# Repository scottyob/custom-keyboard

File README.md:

# custom-keyboard
My very first custom keyboard!

## Goals
* Be really quick to change machines from a work computer, personal computer, and embedded computer
* Have an embeded display for e-mails and custom notifications.

## Designing
[Keyboard Layout Editor](http://www.keyboard-layout-editor.com/) is used to build the layout
[PCB Generator](https://builder.mrkeebs.com/) is used to build the base KiCad templates - Not working
[KiCad plugin](https://github.com/adamws/kicad-kbplacer) Maybe this

## Inspiration
https://github.com/overlordpro-sys/keycool84keyboard
[Designers Guide](https://wiki.ai03.com/books/pcb-design/chapter/pcb-designer-guide)
[Great YouTube Design](https://www.youtube.com/watch?v=8WXpGTIbxlQ) (plus, his name is Scotto!)

## Display options
* This looks small enough and has a large enough resolution to be useful:  https://www.amazon.com/Portable-Computer-Temperature-Raspberry-Monitoring/dp/B0C5CJSM3B/ref=sr_1_15?crid=1Z2TTTSMCJ9M3&dib=eyJ2IjoiMSJ9.twG_gHx_7npwcecLIDkTMz68C16EEFkX2myDhWZpakM4PwJHDKMsepyzzZx5_fr-Fv0QWtuMAJvjoFRniusn_2mAP8U1p1KvTDTy_nIf5XBhxKDMTtR6kEIH5bDDDC3kfiqdF0MrOl_FwFwhKsGs7nZMyqzwkf1SLikeBaauqQMlMwHEYTlBRP9wpbAJ9CpN7bQet1QICcqR2IB1Qb4BmEeEdJr8Al8KNutdiwxeoi11xH34oSaYqEw22Ke8fPJI00CEKSvfC8BukvGODd5jw-uKOd0040SWEzb48uFr6ig.ORM6r5WaZxyWdhVOk3N-LtFBRF50ZFboxtpqMb3Jbdg&dib_tag=se&keywords=stretched%2Bbar%2Bdisplay&qid=1719265894&sprefix=stretched%2Bbar%2Bdisplay%2Caps%2C145&sr=8-15&th=1

## Log
The KeyCool 84 model was used

## BOM
Keys:  https://www.amazon.com/Ranked-Ks-33-Switches-Mechanical-Keyboards/dp/B09WYFZ9RW?source=ps-sl-shoppingads-lpcontext&ref_=fplfs&smid=AH4D7YJ4IREB6&th=1

Switches:  Keychron Low-Profile Keychron Optical White Switch Set:  https://www.amazon.com/Keychron-Low-Profile-Optical-White-Switch/dp/B09F8N5671/ref=asc_df_B09F8N5671/?tag=hyprod-20&linkCode=df0&hvadid=692875362841&hvpos=&hvnetw=g&hvrand=16111957698866127215&hvpone=&hvptwo=&hvqmt=&hvdev=c&hvdvcmdl=&hvlocint=&hvlocphy=9031967&hvtargid=pla-2281435178578&mcid=0d9c4b6c974f36919238ca352fcf1e5d&hvocijid=16111957698866127215-B09F8N5671-&hvexpln=73&gad_source=1&th=1

---
Keys:  https://nuphy.com/products/nuphy-wisteria-t55-low-profile-switches?variant=40519244185709&currency=USD&utm_medium=product_sync&utm_source=google&utm_content=sag_organic&utm_campaign=sag_organic&cmp_id=20374253646&adg_id=&kwd=&device=c&gad_source=1&gclid=CjwKCAjw-O6zBhASEiwAOHeGxY04Fqa9ekofnuaXTJEuknBaLYsXi4nRFtKgb14qA1gg2Q-BrQMgmBoCAmcQAvD_BwE

[200~NuPhy Wisteria Low-profile Switches

**You'll want Gateron KS-33**

Use These:  https://shop.beekeeb.com/product/gateron-low-profile-hotswap-socket/
With this footprint:  https://github.com/siderakb/key-switches.pretty?tab=readme-ov-file#user-content-fn-pth-25bb5443dc34dca477740638b10eb813

Guides:
https://github.com/ebastler/zmk-designguide
this recommends holyiot 18010 or moko mk08a. other people fiddle around with stuff like xiao nrf or even nice!nano (or nice!nano clones)

Keycaps perhaps:
- These are not shine through, but I like them!  https://www.amazon.com/Chocfox-Keyboard-Switches-Mechanical-white-134Keys/dp/B0CQ1ZHDP8/ref=sims_dp_d_dex_ai_speed_loc_mtl-v2_v1_d_sccl_2_5/139-4689362-5463854?pd_rd_w=tRYy4&content-id=amzn1.sym.970de5f6-e09a-4fcf-80c0-0a0041912886&pf_rd_p=970de5f6-e09a-4fcf-80c0-0a0041912886&pf_rd_r=KBXG3AW2HWJMRZ1WNTVA&pd_rd_wg=QhR4F&pd_rd_r=f35a1bc3-d88b-4c73-8d4c-3228ac4289e8&pd_rd_i=B0CQ1ZHDP8&psc=1

- Yeah, I think these keycaps:  https://www.amazon.com/XVX-Profile-Keyboard-Switches-Mechanical/dp/B0BVYV67QS/ref=pd_bxgy_thbs_d_sccl_1/139-4689362-5463854?pd_rd_w=X4Tbp&content-id=amzn1.sym.60707ad7-5cf4-45ed-b044-7f953897a39a&pf_rd_p=60707ad7-5cf4-45ed-b044-7f953897a39a&pf_rd_r=VAWAKCYHR6X9TYQKH0A8&pd_rd_wg=gBP03&pd_rd_r=466d4956-36b8-48f1-ac49-e200315451c7&pd_rd_i=B0BVYV67QS&psc=1

 - Controller

Probably this:  https://makerdiary.com/products/nrf52840-connectkit?variant=43255093035163

# Setup
1. Install [This Plugin](https://github.com/ebastler/marbastlib)
2. 

Footprint for KS-33:  https://shop.beekeeb.com/product/gateron-low-profile-hotswap-socket/

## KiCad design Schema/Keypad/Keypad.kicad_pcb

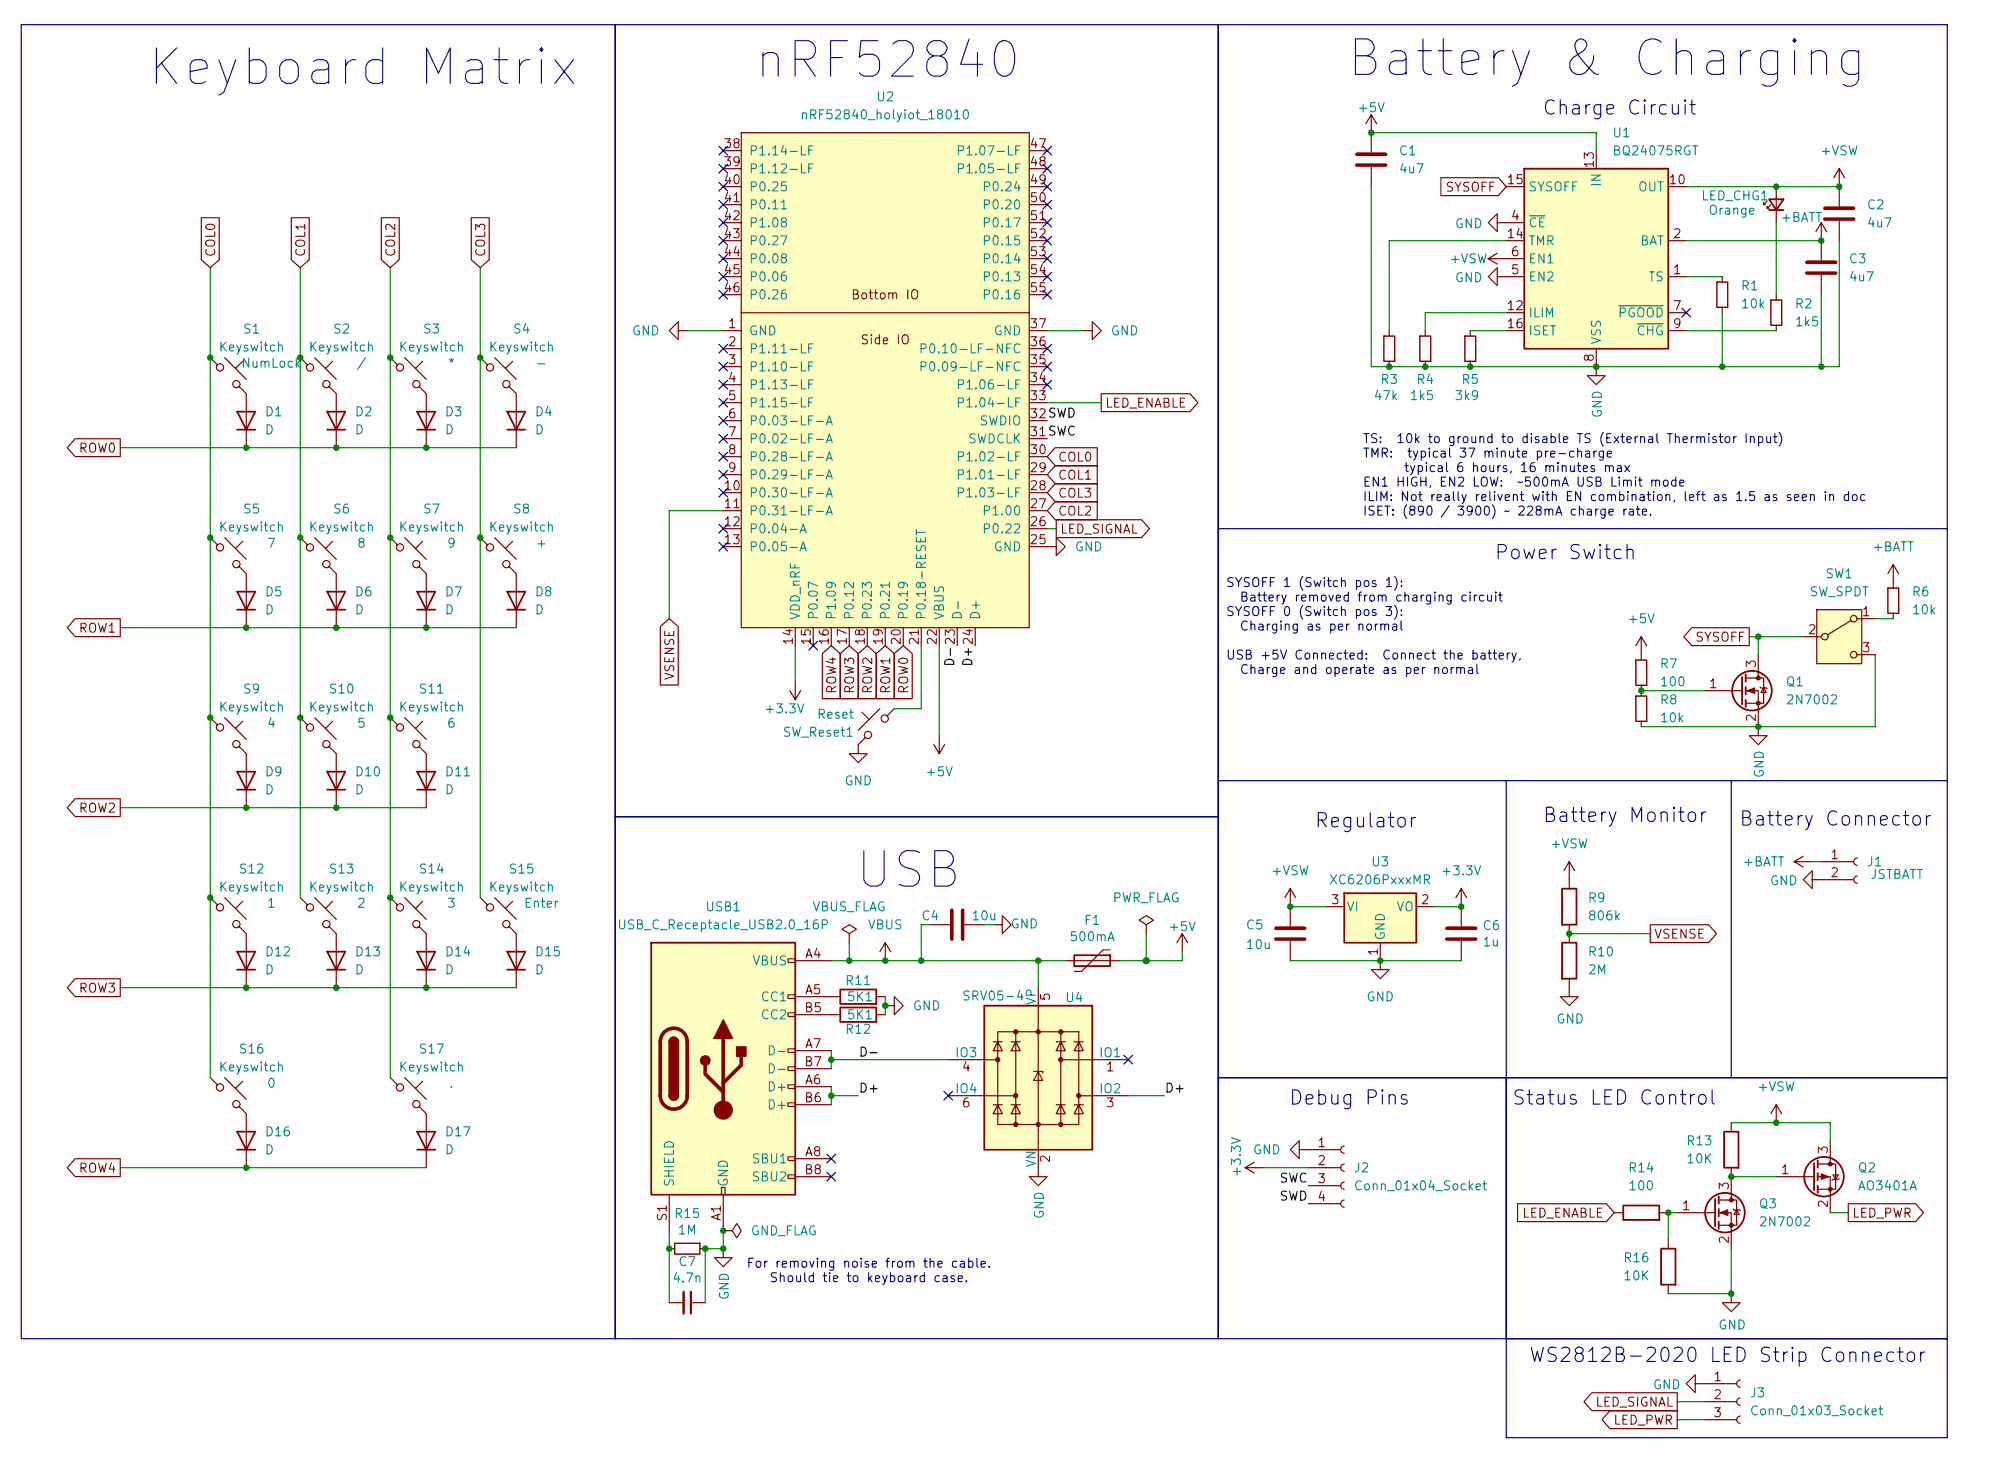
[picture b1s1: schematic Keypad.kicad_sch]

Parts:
C1, C2, C3: 4u7; C_0603_1608Metric
C4, C5: 10u; C_0603_1608Metric; MPN CL10A106KP8NNNC; JLCSMT C19702
C6: 1u; C_0603_1608Metric; MPN CL10A105KB8NNNC; LCSC C15849
C7: 4.7n; C_0805_2012Metric
D1, D2, D3, D4, D5, D6, D7, D8, D9, D10, D11, D12, D13, D14, D15, D16, D17: D; Diode_SOD-123
F1: 500mA; Fuse_0805_2012Metric; MPN SMD0805-050; JLCSMT C66452
J1: JSTBATT; JST_PH_S2B-PH-K_1x02_P2.00mm_Horizontal
J2: Conn_01x04_Socket; PinHeader_1x04_P2.54mm_Vertical
J3: Conn_01x03_Socket; PinSocket_1x03_P2.54mm_Vertical
LED_CHG1: Orange; LED_0603_1608Metric_Pad1.05x0.95mm_HandSolder
Q1, Q3: 2N7002; SOT-23
Q2: AO3401A; SOT-23
R1, R6, R8: 10k; R_0603_1608Metric_Pad0.98x0.95mm_HandSolder
R2, R4: 1k5; R_0603_1608Metric_Pad0.98x0.95mm_HandSolder
R3: 47k; R_0603_1608Metric_Pad0.98x0.95mm_HandSolder
R5: 3k9; R_0603_1608Metric_Pad0.98x0.95mm_HandSolder
R7, R14: 100; R_0603_1608Metric_Pad0.98x0.95mm_HandSolder
R9: 806k; R_0603_1608Metric_Pad0.98x0.95mm_HandSolder
R10: 2M; R_0603_1608Metric_Pad0.98x0.95mm_HandSolder
R11, R12: 5K1; R_0603_1608Metric_Pad0.98x0.95mm_HandSolder
R13, R16: 10K; R_0603_1608Metric_Pad0.98x0.95mm_HandSolder
R15: 1M; R_0603_1608Metric_Pad0.98x0.95mm_HandSolder
S1, S2, S3, S4, S5, S6, S7, S8, S9, S10, S11, S12, S13, S14, S15, S16, S17: Keyswitch; SW_KS33_HS_KS-2P02B01-02_HS_1u
SW1: SW_SPDT; SW_MSK12C02-HB
SW_Reset1: Reset; SW_Push_1P1T_NO_6x6mm_H9.5mm
U1: BQ24075RGT; VQFN-16-1EP_3x3mm_P0.5mm_EP1.6x1.6mm
U2: nRF52840_holyiot_18010
U3: XC6206PxxxMR; SOT-23-3
U4: SRV05-4; SOT-23-6; MPN SRV05-4-P-T7; JLCSMT C85364
USB1: USB_C_Receptacle_USB2.0_16P; USB_C_Receptacle_HRO_TYPE-C-31-M-12

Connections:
+3.3V: C6.2, J2.2, U2.14 (VDD_nRF), U3.2 (VO)
+5V: C1.1, F1.1, R7.1, U1.13 (IN), U2.22 (VBUS)
+BATT: C3.1, J1.1, R6.1, U1.2 (BAT), U1.3 (BAT)
+VSW: C2.1, C5.1, LED_CHG1.2 (A), Q2.3 (D), R9.1, R13.1, U1.6 (EN1), U1.10 (OUT), U1.11 (OUT), U3.3 (VI)
/D+: U2.24 (D+), U4.3 (IO2), USB1.A6 (D+), USB1.B6 (D+)
/D-: U2.23 (D-), U4.4 (IO3), USB1.A7 (D-), USB1.B7 (D-)
/SWC: J2.3, U2.31 (SWDCLK)
/SWD: J2.4, U2.32 (SWDIO)
COL0: S1.1, S5.1, S9.1, S12.1, S16.1, U2.30 (P1.02-LF)
COL1: S2.1, S6.1, S10.1, S13.1, U2.29 (P1.01-LF)
COL2: S3.1, S7.1, S11.1, S14.1, S17.1, U2.27 (P1.00)
COL3: S4.1, S8.1, S15.1, U2.28 (P1.03-LF)
GND: C1.2, C2.2, C3.2, C4.1, C5.2, C6.1, C7.1, J1.2, J2.1, J3.1, Q1.2 (S), Q3.2 (S), R1.2, R3.2, R4.2, R5.2, R8.2, R10.2, R11.2, R12.2, R15.1, R16.2, SW1.3 (C), SW_Reset1.1, U1.4 (~CE), U1.5 (EN2), U1.8 (VSS), U1.17 (VSS), U2.1 (GND), U2.25 (GND), U2.37 (GND), U3.1 (GND), U4.2 (VN), USB1.A1 (GND), USB1.A12 (GND), USB1.B1 (GND), USB1.B12 (GND)
LED_ENABLE: R14.1, U2.33 (P1.04-LF)
LED_PWR: J3.3, Q2.2 (S)
LED_SIGNAL: J3.2, U2.26 (P0.22)
unnamed: D1.2 (A), S1.2
unnamed: D2.2 (A), S2.2
unnamed: D3.2 (A), S3.2
unnamed: D4.2 (A), S4.2
unnamed: D5.2 (A), S5.2
unnamed: D6.2 (A), S6.2
unnamed: D7.2 (A), S7.2
unnamed: D8.2 (A), S8.2
unnamed: D9.2 (A), S9.2
unnamed: D10.2 (A), S10.2
unnamed: D11.2 (A), S11.2
unnamed: D12.2 (A), S12.2
unnamed: D13.2 (A), S13.2
unnamed: D14.2 (A), S14.2
unnamed: D15.2 (A), S15.2
unnamed: D16.2 (A), S16.2
unnamed: D17.2 (A), S17.2
unnamed: LED_CHG1.1 (K), R2.1
unnamed: Q1.1 (G), R7.2, R8.1
unnamed: Q2.1 (G), Q3.3 (D), R13.2
unnamed: Q3.1 (G), R14.2, R16.1
unnamed: R6.2, SW1.1 (A)
unnamed: R4.1, U1.12 (ILIM)
unnamed: R5.1, U1.16 (ISET)
unnamed: R3.1, U1.14 (TMR)
unnamed: R1.1, U1.1 (TS)
unnamed: R2.2, U1.9 (~CHG)
unnamed: SW_Reset1.2, U2.21 (P0.18-RESET)
unnamed: R11.1, USB1.A5 (CC1)
unnamed: R12.1, USB1.B5 (CC2)
unnamed: C7.2, R15.2, USB1.S1 (SHIELD)
ROW0: D1.1 (K), D2.1 (K), D3.1 (K), D4.1 (K), U2.20 (P0.19)
ROW1: D5.1 (K), D6.1 (K), D7.1 (K), D8.1 (K), U2.19 (P0.21)
ROW2: D9.1 (K), D10.1 (K), D11.1 (K), U2.18 (P0.23)
ROW3: D12.1 (K), D13.1 (K), D14.1 (K), D15.1 (K), U2.17 (P0.12)
ROW4: D16.1 (K), D17.1 (K), U2.16 (P1.09)
SYSOFF: Q1.3 (D), SW1.2 (B), U1.15 (SYSOFF)
VBUS: C4.2, F1.2, U4.5 (VP), USB1.A4 (VBUS), USB1.A9 (VBUS), USB1.B4 (VBUS), USB1.B9 (VBUS)
VSENSE: R9.2, R10.1, U2.11 (P0.31-LF-A)

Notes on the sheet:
Status LED Control
WS2812B-2020 LED Strip Connector
USB
Battery & Charging
nRF52840
Charge Circuit
Battery Connector
Power Switch
Keyboard Matrix
SYSOFF 1 (Switch pos 1): Battery removed from charging circuit SYSOFF 0 (Switch pos 3): Charging as per normal USB +5V Connected: Connect the battery, Charge and operate as per normal
Debug Pins
For removing noise from the cable. Should tie to keyboard case.
Battery Monitor
Regulator
TS: 10k to ground to disable TS (External Thermistor Input) TMR: typical 37 minute pre-charge typical 6 hours, 16 minutes max EN1 HIGH, EN2 LOW: ~500mA USB Limit mode ILIM: Not really relivent with EN combination, left as 1.5 as seen in doc ISET: (890 / 3900) ~ 228mA charge rate.

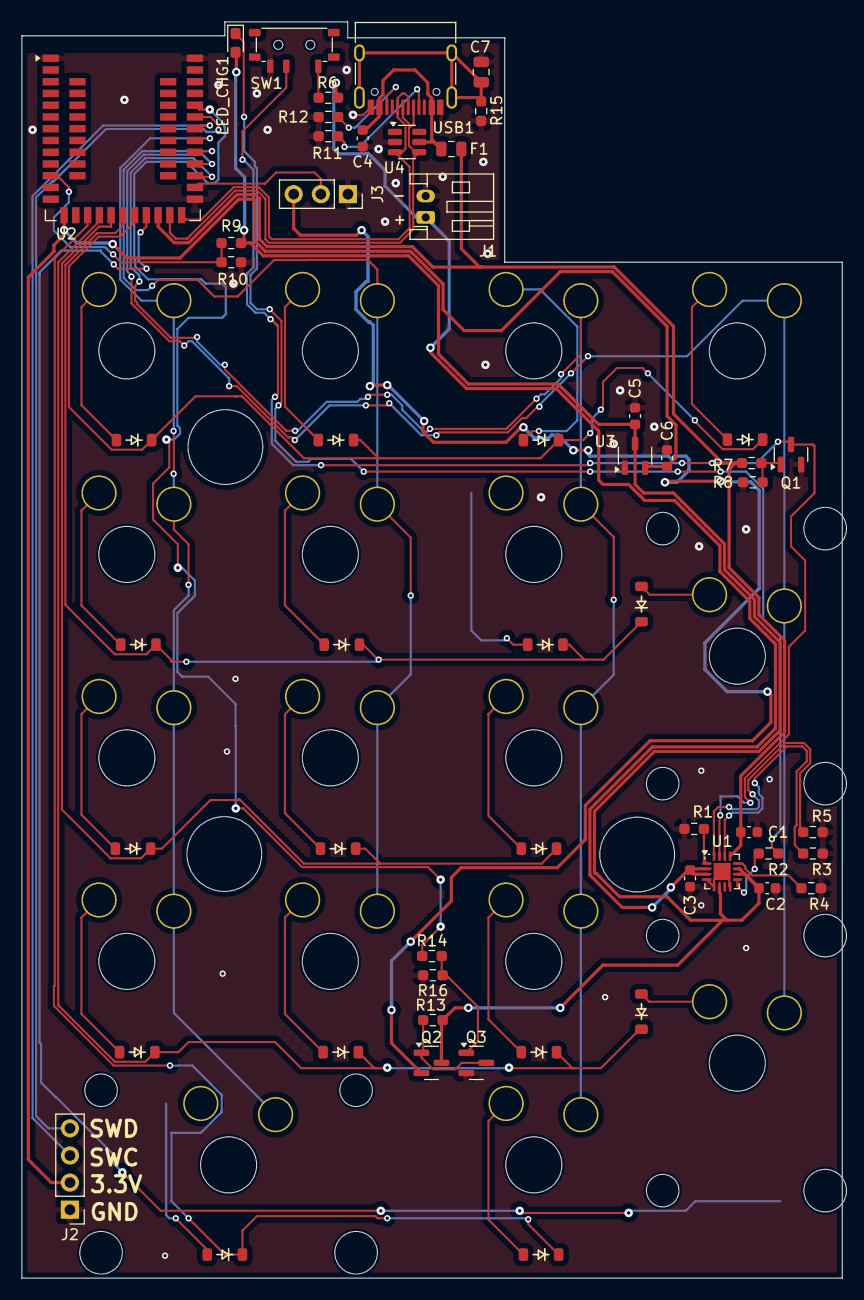
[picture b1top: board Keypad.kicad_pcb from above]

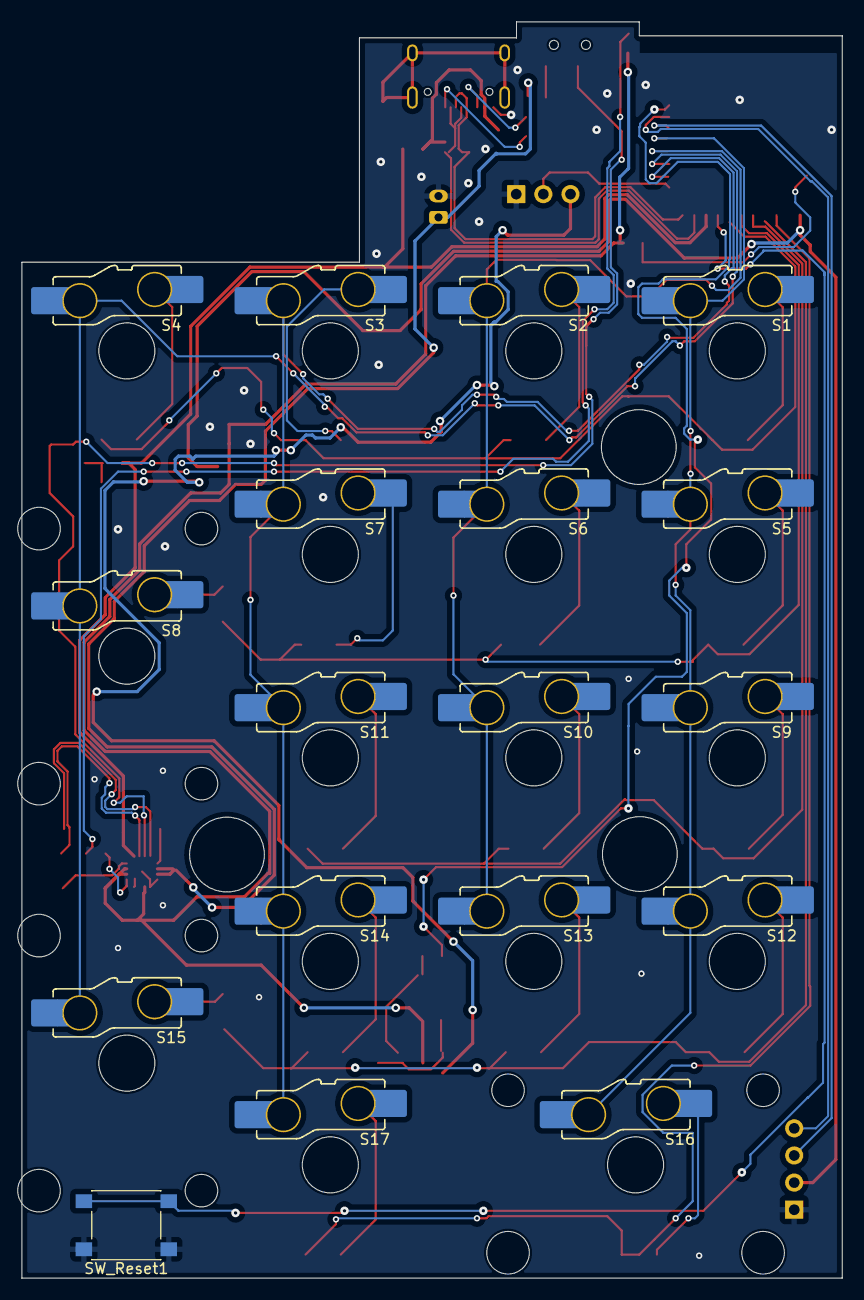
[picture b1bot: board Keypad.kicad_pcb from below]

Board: 2 copper layers, 76.8 x 117.6 mm, 72 parts (18 on the bottom side), 55 nets.

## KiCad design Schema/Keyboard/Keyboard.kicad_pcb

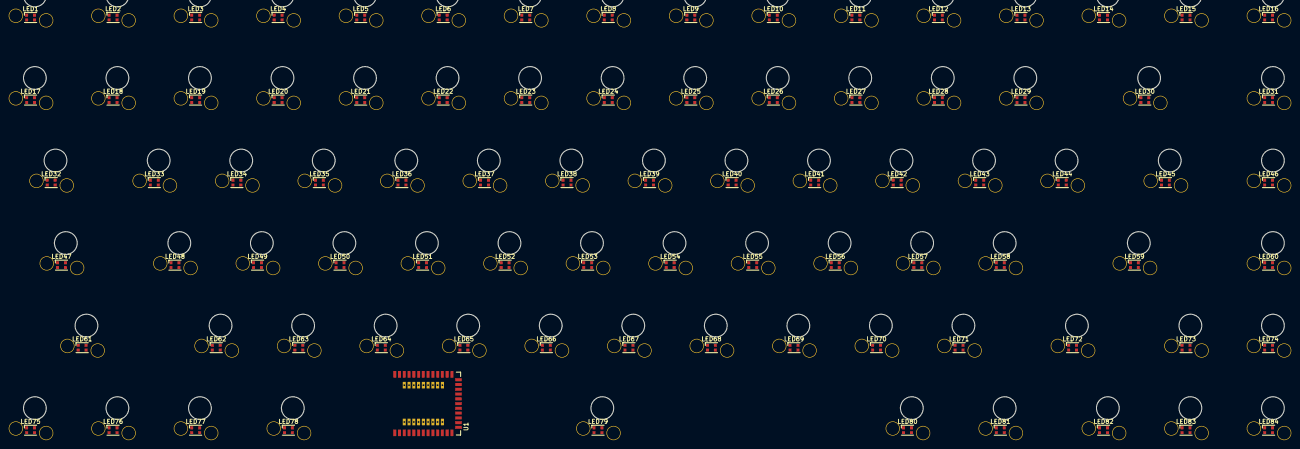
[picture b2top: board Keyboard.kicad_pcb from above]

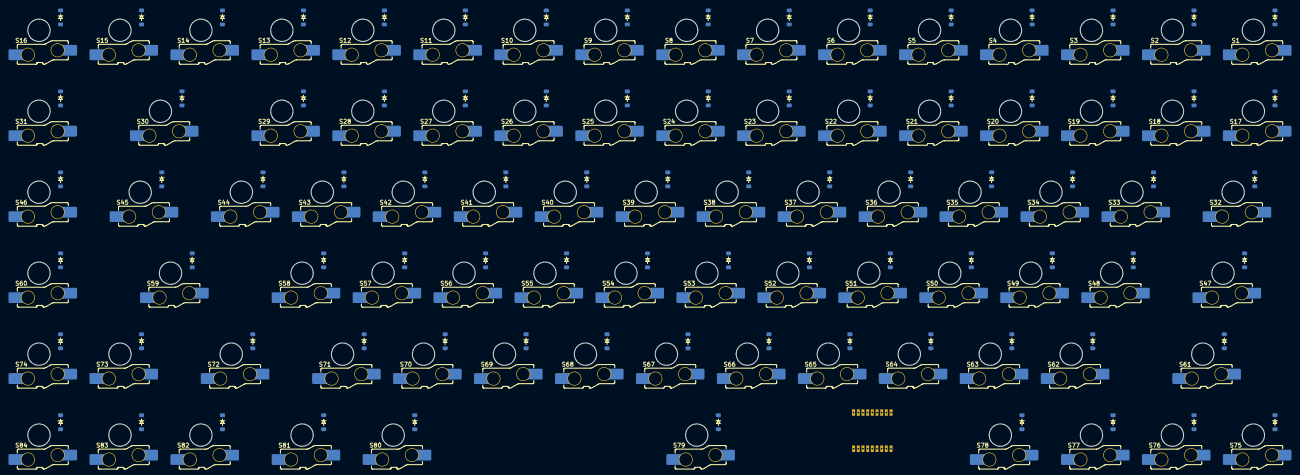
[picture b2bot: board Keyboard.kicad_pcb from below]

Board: 2 copper layers, 253 parts (168 on the bottom side), 191 nets, no tracks yet.

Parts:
D1, D2, D3, D4, D5, D6, D7, D8, D9, D10, D11, D12, D13, D14, D15, D16, D17, D18, D19, D20, D21, D22, D23, D24, D25, D26, D27, D28, D29, D30, D31, D32, D33, D34, D35, D36, D37, D38, D39, D40, D41, D42, D43, D44, D45, D46, D47, D48, D49, D50, D51, D52, D53, D54, D55, D56, D57, D58, D59, D60, D61, D62, D63, D64, D65, D66, D67, D68, D69, D70, D71, D72, D73, D74, D75, D76, D77, D78, D79, D80, D81, D82, D83, D84: D; Diode_SOD-123
LED1, LED2, LED3, LED4, LED5, LED6, LED7, LED8, LED9, LED10, LED11, LED12, LED13, LED14, LED15, LED16, LED17, LED18, LED19, LED20, LED21, LED22, LED23, LED24, LED25, LED26, LED27, LED28, LED29, LED30, LED31, LED32, LED33, LED34, LED35, LED36, LED37, LED38, LED39, LED40, LED41, LED42, LED43, LED44, LED45, LED46, LED47, LED48, LED49, LED50, LED51, LED52, LED53, LED54, LED55, LED56, LED57, LED58, LED59, LED60, LED61, LED62, LED63, LED64, LED65, LED66, LED67, LED68, LED69, LED70, LED71, LED72, LED73, LED74, LED75, LED76, LED77, LED78, LED79, LED80, LED81, LED82, LED83, LED84: WS2812B-2020; LED_WS2812B-2020_PLCC4_2.0x2.0mm
S1, S2, S3, S4, S5, S6, S7, S8, S9, S10, S11, S12, S13, S14, S15, S16, S17, S18, S19, S20, S21, S22, S23, S24, S25, S26, S27, S28, S29, S30, S31, S32, S33, S34, S35, S36, S37, S38, S39, S40, S41, S42, S43, S44, S45, S46, S47, S48, S49, S50, S51, S52, S53, S54, S55, S56, S57, S58, S59, S60, S61, S62, S63, S64, S65, S66, S67, S68, S69, S70, S71, S72, S73, S74, S75, S76, S77, S78, S79, S80, S81, S82, S83, S84: Keyswitch; SW_KS33_HS_KS-2P02B01-02_HS_1u
U1: nRF52840_holyiot_18010

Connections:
+5V: LED1.4 (VDD), LED2.4 (VDD), LED3.4 (VDD), LED4.4 (VDD), LED5.4 (VDD), LED6.4 (VDD), LED7.4 (VDD), LED8.4 (VDD), LED9.4 (VDD), LED10.4 (VDD), LED11.4 (VDD), LED12.4 (VDD), LED13.4 (VDD), LED14.4 (VDD), LED15.4 (VDD), LED16.4 (VDD), LED17.4 (VDD), LED18.4 (VDD), LED19.4 (VDD), LED20.4 (VDD), LED21.4 (VDD), LED22.4 (VDD), LED23.4 (VDD), LED24.4 (VDD), LED25.4 (VDD), LED26.4 (VDD), LED27.4 (VDD), LED28.4 (VDD), LED29.4 (VDD), LED30.4 (VDD), LED31.4 (VDD), LED32.4 (VDD), LED33.4 (VDD), LED34.4 (VDD), LED35.4 (VDD), LED36.4 (VDD), LED37.4 (VDD), LED38.4 (VDD), LED39.4 (VDD), LED40.4 (VDD), LED41.4 (VDD), LED42.4 (VDD), LED43.4 (VDD), LED44.4 (VDD), LED45.4 (VDD), LED46.4 (VDD), LED47.4 (VDD), LED48.4 (VDD), LED49.4 (VDD), LED50.4 (VDD), LED51.4 (VDD), LED52.4 (VDD), LED53.4 (VDD), LED54.4 (VDD), LED55.4 (VDD), LED56.4 (VDD), LED57.4 (VDD), LED58.4 (VDD), LED59.4 (VDD), LED60.4 (VDD), LED61.4 (VDD), LED62.4 (VDD), LED63.4 (VDD), LED64.4 (VDD), LED65.4 (VDD), LED66.4 (VDD), LED67.4 (VDD), LED68.4 (VDD), LED69.4 (VDD), LED70.4 (VDD), LED71.4 (VDD), LED72.4 (VDD), LED73.4 (VDD), LED74.4 (VDD), LED75.4 (VDD), LED76.4 (VDD), LED77.4 (VDD), LED78.4 (VDD), LED79.4 (VDD), LED80.4 (VDD), LED81.4 (VDD), LED82.4 (VDD), LED83.4 (VDD), LED84.4 (VDD)
COL0: S1.1, S17.1, S32.1, S47.1, S75.1
COL1: S2.1, S18.1, S61.1, S76.1
COL2: S3.1, S19.1, S33.1, S48.1, S62.1, S77.1
COL3: S4.1, S20.1, S34.1, S49.1, S63.1, S78.1
COL4: S5.1, S21.1, S35.1, S50.1, S64.1
COL5: S6.1, S22.1, S36.1, S51.1, S65.1
COL6: S7.1, S23.1, S37.1, S52.1, S66.1, S79.1
COL7: S8.1, S24.1, S38.1, S53.1, S67.1
COL8: S9.1, S25.1, S39.1, S54.1, S68.1
COL9: S10.1, S26.1, S40.1, S55.1, S69.1
COL10: S11.1, S27.1, S41.1, S56.1, S70.1, S80.1
COL11: S12.1, S28.1, S42.1, S57.1, S71.1, S81.1
COL12: S13.1, S29.1, S43.1, S58.1
COL13: S14.1, S44.1, S59.1, S72.1, S82.1
COL14: S15.1, S30.1, S45.1, S73.1, S83.1
COL15: S16.1, S31.1, S46.1, S60.1, S74.1, S84.1
GND: LED1.2 (VSS), LED2.2 (VSS), LED3.2 (VSS), LED4.2 (VSS), LED5.2 (VSS), LED6.2 (VSS), LED7.2 (VSS), LED8.2 (VSS), LED9.2 (VSS), LED10.2 (VSS), LED11.2 (VSS), LED12.2 (VSS), LED13.2 (VSS), LED14.2 (VSS), LED15.2 (VSS), LED16.2 (VSS), LED17.2 (VSS), LED18.2 (VSS), LED19.2 (VSS), LED20.2 (VSS), LED21.2 (VSS), LED22.2 (VSS), LED23.2 (VSS), LED24.2 (VSS), LED25.2 (VSS), LED26.2 (VSS), LED27.2 (VSS), LED28.2 (VSS), LED29.2 (VSS), LED30.2 (VSS), LED31.2 (VSS), LED32.2 (VSS), LED33.2 (VSS), LED34.2 (VSS), LED35.2 (VSS), LED36.2 (VSS), LED37.2 (VSS), LED38.2 (VSS), LED39.2 (VSS), LED40.2 (VSS), LED41.2 (VSS), LED42.2 (VSS), LED43.2 (VSS), LED44.2 (VSS), LED45.2 (VSS), LED46.2 (VSS), LED47.2 (VSS), LED48.2 (VSS), LED49.2 (VSS), LED50.2 (VSS), LED51.2 (VSS), LED52.2 (VSS), LED53.2 (VSS), LED54.2 (VSS), LED55.2 (VSS), LED56.2 (VSS), LED57.2 (VSS), LED58.2 (VSS), LED59.2 (VSS), LED60.2 (VSS), LED61.2 (VSS), LED62.2 (VSS), LED63.2 (VSS), LED64.2 (VSS), LED65.2 (VSS), LED66.2 (VSS), LED67.2 (VSS), LED68.2 (VSS), LED69.2 (VSS), LED70.2 (VSS), LED71.2 (VSS), LED72.2 (VSS), LED73.2 (VSS), LED74.2 (VSS), LED75.2 (VSS), LED76.2 (VSS), LED77.2 (VSS), LED78.2 (VSS), LED79.2 (VSS), LED80.2 (VSS), LED81.2 (VSS), LED82.2 (VSS), LED83.2 (VSS), LED84.2 (VSS)
unnamed: D1.2 (A), S1.2
unnamed: D2.2 (A), S2.2
unnamed: D3.2 (A), S3.2
unnamed: D4.2 (A), S4.2
unnamed: D5.2 (A), S5.2
unnamed: D6.2 (A), S6.2
unnamed: D7.2 (A), S7.2
unnamed: D8.2 (A), S8.2
unnamed: D9.2 (A), S9.2
unnamed: D10.2 (A), S10.2
unnamed: D11.2 (A), S11.2
unnamed: D12.2 (A), S12.2
unnamed: D13.2 (A), S13.2
unnamed: D14.2 (A), S14.2
unnamed: D15.2 (A), S15.2
unnamed: D16.2 (A), S16.2
unnamed: D17.2 (A), S17.2
unnamed: D18.2 (A), S18.2
unnamed: D19.2 (A), S19.2
unnamed: D20.2 (A), S20.2
unnamed: D21.2 (A), S21.2
unnamed: D22.2 (A), S22.2
unnamed: D23.2 (A), S23.2
unnamed: D24.2 (A), S24.2
unnamed: D25.2 (A), S25.2
unnamed: D26.2 (A), S26.2
unnamed: D27.2 (A), S27.2
unnamed: D28.2 (A), S28.2
unnamed: D29.2 (A), S29.2
unnamed: D30.2 (A), S30.2
unnamed: D31.2 (A), S31.2
unnamed: D32.2 (A), S32.2
unnamed: D33.2 (A), S33.2
unnamed: D34.2 (A), S34.2
unnamed: D35.2 (A), S35.2
unnamed: D36.2 (A), S36.2
unnamed: D37.2 (A), S37.2
unnamed: D38.2 (A), S38.2
unnamed: D39.2 (A), S39.2
unnamed: D40.2 (A), S40.2
unnamed: D41.2 (A), S41.2
unnamed: D42.2 (A), S42.2
unnamed: D43.2 (A), S43.2
unnamed: D44.2 (A), S44.2
unnamed: D45.2 (A), S45.2
unnamed: D46.2 (A), S46.2
unnamed: D47.2 (A), S47.2
unnamed: D48.2 (A), S48.2
unnamed: D49.2 (A), S49.2
unnamed: D50.2 (A), S50.2
unnamed: D51.2 (A), S51.2
unnamed: D52.2 (A), S52.2
unnamed: D53.2 (A), S53.2
unnamed: D54.2 (A), S54.2
unnamed: D55.2 (A), S55.2
unnamed: D56.2 (A), S56.2
unnamed: D57.2 (A), S57.2
unnamed: D58.2 (A), S58.2
unnamed: D59.2 (A), S59.2
unnamed: D60.2 (A), S60.2
unnamed: D61.2 (A), S61.2
unnamed: D62.2 (A), S62.2
unnamed: D63.2 (A), S63.2
unnamed: D64.2 (A), S64.2
unnamed: D65.2 (A), S65.2
unnamed: D66.2 (A), S66.2
unnamed: D67.2 (A), S67.2
unnamed: D68.2 (A), S68.2
unnamed: D69.2 (A), S69.2
unnamed: D70.2 (A), S70.2
unnamed: D71.2 (A), S71.2
unnamed: D72.2 (A), S72.2
unnamed: D73.2 (A), S73.2
unnamed: D74.2 (A), S74.2
unnamed: D75.2 (A), S75.2
unnamed: D76.2 (A), S76.2
unnamed: D77.2 (A), S77.2
unnamed: D78.2 (A), S78.2
unnamed: D79.2 (A), S79.2
unnamed: D80.2 (A), S80.2
unnamed: D81.2 (A), S81.2
unnamed: D82.2 (A), S82.2
unnamed: D83.2 (A), S83.2
unnamed: D84.2 (A), S84.2
unnamed: LED1.1 (DOUT), LED2.3 (DIN)
unnamed: LED2.1 (DOUT), LED3.3 (DIN)
unnamed: LED3.1 (DOUT), LED4.3 (DIN)
unnamed: LED4.1 (DOUT), LED5.3 (DIN)
unnamed: LED5.1 (DOUT), LED6.3 (DIN)
unnamed: LED6.1 (DOUT), LED7.3 (DIN)
unnamed: LED7.1 (DOUT), LED8.3 (DIN)
unnamed: LED8.1 (DOUT), LED9.3 (DIN)
unnamed: LED9.1 (DOUT), LED10.3 (DIN)
unnamed: LED10.1 (DOUT), LED11.3 (DIN)
unnamed: LED11.1 (DOUT), LED12.3 (DIN)
unnamed: LED12.1 (DOUT), LED13.3 (DIN)
unnamed: LED13.1 (DOUT), LED14.3 (DIN)
unnamed: LED14.1 (DOUT), LED15.3 (DIN)
unnamed: LED15.1 (DOUT), LED16.3 (DIN)
unnamed: LED16.1 (DOUT), LED17.3 (DIN)
unnamed: LED17.1 (DOUT), LED18.3 (DIN)
unnamed: LED18.1 (DOUT), LED19.3 (DIN)
unnamed: LED19.1 (DOUT), LED20.3 (DIN)
unnamed: LED20.1 (DOUT), LED21.3 (DIN)
unnamed: LED21.1 (DOUT), LED22.3 (DIN)
unnamed: LED22.1 (DOUT), LED23.3 (DIN)
unnamed: LED23.1 (DOUT), LED24.3 (DIN)
unnamed: LED24.1 (DOUT), LED25.3 (DIN)
unnamed: LED25.1 (DOUT), LED26.3 (DIN)
unnamed: LED26.1 (DOUT), LED27.3 (DIN)
unnamed: LED27.1 (DOUT), LED28.3 (DIN)
unnamed: LED28.1 (DOUT), LED29.3 (DIN)
unnamed: LED29.1 (DOUT), LED30.3 (DIN)
unnamed: LED30.1 (DOUT), LED31.3 (DIN)
unnamed: LED31.1 (DOUT), LED32.3 (DIN)
unnamed: LED32.1 (DOUT), LED33.3 (DIN)
unnamed: LED33.1 (DOUT), LED34.3 (DIN)
unnamed: LED34.1 (DOUT), LED35.3 (DIN)
unnamed: LED35.1 (DOUT), LED36.3 (DIN)
unnamed: LED36.1 (DOUT), LED37.3 (DIN)
unnamed: LED37.1 (DOUT), LED38.3 (DIN)
unnamed: LED38.1 (DOUT), LED39.3 (DIN)
unnamed: LED39.1 (DOUT), LED40.3 (DIN)
unnamed: LED40.1 (DOUT), LED41.3 (DIN)
unnamed: LED41.1 (DOUT), LED42.3 (DIN)
unnamed: LED42.1 (DOUT), LED43.3 (DIN)
unnamed: LED43.1 (DOUT), LED44.3 (DIN)
unnamed: LED44.1 (DOUT), LED45.3 (DIN)
unnamed: LED45.1 (DOUT), LED46.3 (DIN)
unnamed: LED46.1 (DOUT), LED47.3 (DIN)
unnamed: LED47.1 (DOUT), LED48.3 (DIN)
unnamed: LED48.1 (DOUT), LED49.3 (DIN)
unnamed: LED49.1 (DOUT), LED50.3 (DIN)
unnamed: LED50.1 (DOUT), LED51.3 (DIN)
unnamed: LED51.1 (DOUT), LED52.3 (DIN)
unnamed: LED52.1 (DOUT), LED53.3 (DIN)
unnamed: LED53.1 (DOUT), LED54.3 (DIN)
unnamed: LED54.1 (DOUT), LED55.3 (DIN)
unnamed: LED55.1 (DOUT), LED56.3 (DIN)
unnamed: LED56.1 (DOUT), LED57.3 (DIN)
unnamed: LED57.1 (DOUT), LED58.3 (DIN)
unnamed: LED58.1 (DOUT), LED59.3 (DIN)
unnamed: LED59.1 (DOUT), LED60.3 (DIN)
unnamed: LED60.1 (DOUT), LED61.3 (DIN)
unnamed: LED61.1 (DOUT), LED62.3 (DIN)
unnamed: LED62.1 (DOUT), LED63.3 (DIN)
unnamed: LED63.1 (DOUT), LED64.3 (DIN)
unnamed: LED64.1 (DOUT), LED65.3 (DIN)
unnamed: LED65.1 (DOUT), LED66.3 (DIN)
unnamed: LED66.1 (DOUT), LED67.3 (DIN)
unnamed: LED67.1 (DOUT), LED68.3 (DIN)
unnamed: LED68.1 (DOUT), LED69.3 (DIN)
unnamed: LED69.1 (DOUT), LED70.3 (DIN)
unnamed: LED70.1 (DOUT), LED71.3 (DIN)
unnamed: LED71.1 (DOUT), LED72.3 (DIN)
unnamed: LED72.1 (DOUT), LED73.3 (DIN)
unnamed: LED73.1 (DOUT), LED74.3 (DIN)
unnamed: LED74.1 (DOUT), LED75.3 (DIN)
unnamed: LED75.1 (DOUT), LED76.3 (DIN)
unnamed: LED76.1 (DOUT), LED77.3 (DIN)
unnamed: LED77.1 (DOUT), LED78.3 (DIN)
unnamed: LED78.1 (DOUT), LED79.3 (DIN)
unnamed: LED79.1 (DOUT), LED80.3 (DIN)
unnamed: LED80.1 (DOUT), LED81.3 (DIN)
unnamed: LED81.1 (DOUT), LED82.3 (DIN)
unnamed: LED82.1 (DOUT), LED83.3 (DIN)
unnamed: LED83.1 (DOUT), LED84.3 (DIN)
ROW0: D1.1 (K), D2.1 (K), D3.1 (K), D4.1 (K), D5.1 (K), D6.1 (K), D7.1 (K), D8.1 (K), D9.1 (K), D10.1 (K), D11.1 (K), D12.1 (K), D13.1 (K), D14.1 (K), D15.1 (K), D16.1 (K)
ROW1: D17.1 (K), D18.1 (K), D19.1 (K), D20.1 (K), D21.1 (K), D22.1 (K), D23.1 (K), D24.1 (K), D25.1 (K), D26.1 (K), D27.1 (K), D28.1 (K), D29.1 (K), D30.1 (K), D31.1 (K)
ROW2: D32.1 (K), D33.1 (K), D34.1 (K), D35.1 (K), D36.1 (K), D37.1 (K), D38.1 (K), D39.1 (K), D40.1 (K), D41.1 (K), D42.1 (K), D43.1 (K), D44.1 (K), D45.1 (K), D46.1 (K)
ROW3: D47.1 (K), D48.1 (K), D49.1 (K), D50.1 (K), D51.1 (K), D52.1 (K), D53.1 (K), D54.1 (K), D55.1 (K), D56.1 (K), D57.1 (K), D58.1 (K), D59.1 (K), D60.1 (K)
ROW4: D61.1 (K), D62.1 (K), D63.1 (K), D64.1 (K), D65.1 (K), D66.1 (K), D67.1 (K), D68.1 (K), D69.1 (K), D70.1 (K), D71.1 (K), D72.1 (K), D73.1 (K), D74.1 (K)
ROW5: D75.1 (K), D76.1 (K), D77.1 (K), D78.1 (K), D79.1 (K), D80.1 (K), D81.1 (K), D82.1 (K), D83.1 (K), D84.1 (K)

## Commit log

2024-09-06 Updating Schema
2024-09-07 Updating with enclosure
